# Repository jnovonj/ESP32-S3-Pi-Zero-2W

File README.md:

# ESP32-S3 Pi Zero 2 W Development Board

A compact, custom 4-layer development board built around the **ESP32-S3-WROOM-1** module, designed specifically to match the form factor and mounting layout of the **Raspberry Pi Zero 2 W**.

---

## 🚀 Key Features

* **Core Module:** Espressif **ESP32-S3-WROOM-1** (Wi-Fi 802.11 b/g/n and Bluetooth 5 / BLE) with onboard antenna.
* **Form Factor:** Drop-in compatible with Raspberry Pi Zero 2 W mounting holes and physical dimensions.
* **Dual USB-C Connectivity:**
  * **USB OTG:** Direct connection to ESP32-S3 native USB pins.
  * **USB-to-UART:** Built around the **CH343K** serial converter for flashing, debugging, and auto-reset circuitry (via dual NPN transistor configuration).
* **Power Supply:** High-efficiency **LDL1117S33R** 3.3V linear regulator powered via 5V VBUS.
* **Peripherals:** Onboard **WS2812B-Mini** addressable RGB LED for status telemetry.
* **Expansion:** 40-pin GPIO header matching standard Raspberry Pi pinout conventions.
* **Protection:** ESD protection via multiple bidirectional TVS diodes (`LESD3Z5.0C`) on data lines.

---

## ⚙️ Board Stackup (4-Layer PCB)

Designed for optimized signal integrity and solid power/ground planes:
1. **F.Cu (Top Layer):** Components and primary signal routing.
2. **In1.Cu (Internal Plane 1):** Dedicated solid **GND** plane.
3. **In2.Cu (Internal Plane 2):** Power distribution plane (`+3.3V` / `+5V`).
4. **B.Cu (Bottom Layer):** Secondary signal traces and stitching ground paths.

---

## 📂 Repository Structure

```text
├── 3D models/                # STEP models for mechanical enclosures and visualization
├── BOM/                      # Bill of Materials for manufacturing and sourcing
├── CPL/                      # Component Placement List (Pick and Place files)
├── Library/                  # Custom schematic symbols and footprints
├── database/                 # Component database files
├── images/                   # Render previews and visual assets
│   └── ESP32-S3-Pi-Zero-2W.png  # 3D PCB render preview
├── ESP32 S3 Pi Zero 2 W.kicad_pro   # KiCad project file
├── ESP32 S3 Pi Zero 2 W.kicad_sch   # Schematic design file
└── ESP32 S3 Pi Zero 2 W.kicad_pcb   # 4-layer PCB layout file

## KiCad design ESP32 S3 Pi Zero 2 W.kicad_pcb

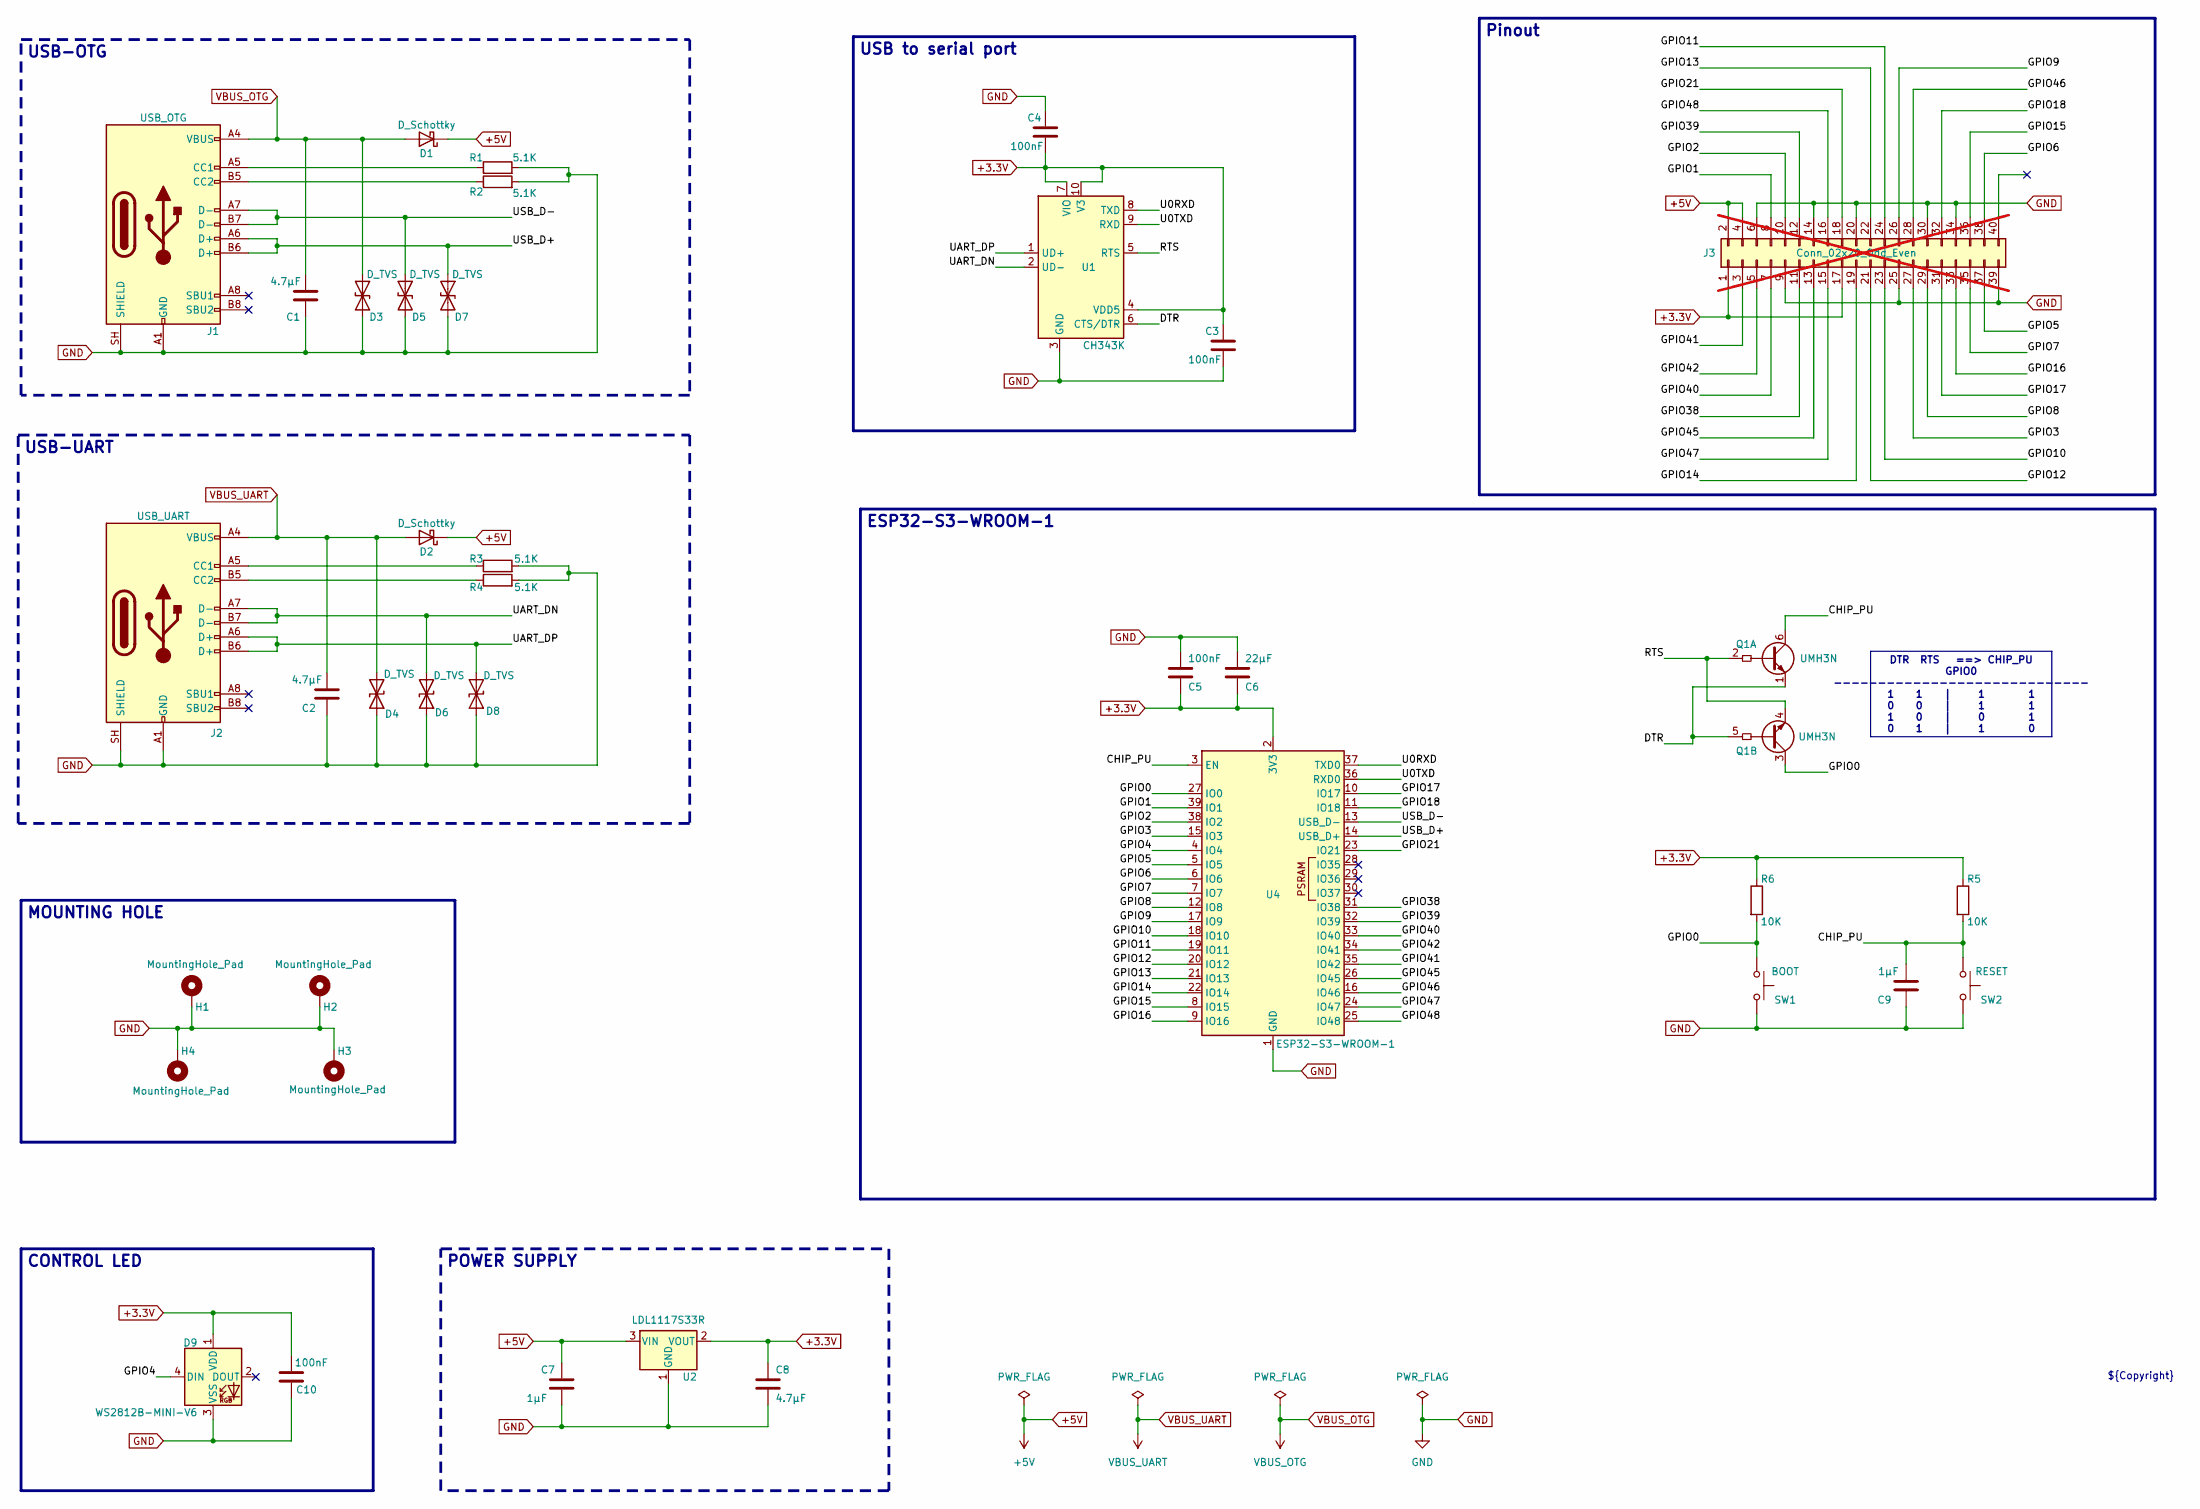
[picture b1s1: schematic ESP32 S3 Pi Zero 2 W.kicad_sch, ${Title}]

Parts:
C1, C2: 4.7µF; C_0603_1608Metric_Pad1.08x0.95mm_HandSolder; MFR.Part # HQ CA0149362
C3, C4, C10: 100nF; C_0603_1608Metric_Pad1.08x0.95mm_HandSolder; MFR.Part # HQ CA0001420
C5: 100nF; C_0603_1608Metric_Pad1.08x0.95mm_HandSolder; Mfr. Part # GRM188R71H104JA93D
C6: 22μF; C_0603_1608Metric_Pad1.08x0.95mm_HandSolder; Mfr. Part # CL10A226MP8NUNE
C7: 1μF; C_0603_1608Metric_Pad1.08x0.95mm_HandSolder; MFR.Part # HQ CA0137201
C8: 4.7µF; C_0603_1608Metric_Pad1.08x0.95mm_HandSolder; MFR.Part # HQ CA0001420
C9: 1µF; C_0603_1608Metric_Pad1.08x0.95mm_HandSolder; MFR.Part # HQ CA0137201
D1, D2: D_Schottky; D_SOD-323_HandSoldering; MFR.Part # HQ DS0183206
D3, D4, D5, D6, D7, D8: D_TVS; D_SOD-323_HandSoldering; MFR.Part # HQ UN0003855
D9: WS2812B-MINI-V6; LED_WS2812B-Mini_PLCC4_3.5x3.5mm; MFR.Part # HQ PH44591203
H1, H2, H3, H4: MountingHole_Pad; MountingHole_2.7mm_M2.5_Pad_Via
J1: USB_OTG; USB_C_Receptacle_GCT_USB4105-xx-A_16P_TopMnt_Horizontal; MFR.Part # HQ ZHLM0001696
J2: USB_UART; USB_C_Receptacle_GCT_USB4105-xx-A_16P_TopMnt_Horizontal; MFR.Part # HQ ZHLM0001696
J3: Conn_02x20_Odd_Even; PinHeader_2x20_P2.54mm_Vertical; Mfr. Part # 1; not fitted
Q1: UMH3N; SOT-363_SC-70-6; MFR.Part # HQ DS0127880
R1, R2, R3, R4: 5.1K; R_0603_1608Metric_Pad0.98x0.95mm_HandSolder; MFR.Part # HQ RE0010352
R5, R6: 10K; R_0603_1608Metric_Pad0.98x0.95mm_HandSolder; MFR.Part # HQ RE0023891
SW1: BOOT; SW_SPST_B3U-1000P; MFR.Part # HQ SW0036094
SW2: RESET; SW_SPST_B3U-1000P; MFR.Part # HQ SW0036094
U1: CH343K; SSOP-10-1EP_3.9x4.9mm_P1mm_EP2.1x3.3mm; Mfr. Part # CH343K
U2: LDL1117S33R; SOT-223-3_TabPin2; MFR.Part # HQ IC0414375
U4: ESP32-S3-WROOM-1; MFR.Part # HQ ZHLM0347370

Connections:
+3.3V: C3.1, C4.2, C5.1, C6.1, C8.1, C10.2, D9.1 (VDD), J3.1, J3.17, R5.1, R6.1, U1.4 (VDD5), U1.7 (VIO), U1.10 (V3), U2.2 (VOUT), U4.2 (3V3)
+5V: C7.1, D1.1 (K), D2.1 (K), J3.2, J3.4, U2.3 (VIN)
/CHIP_PU: C9.1, Q1.6 (C1), R5.2, SW2.1, U4.3 (EN)
/DTR: Q1.1 (E1), Q1.5 (B2), U1.6 (CTS/DTR)
/GPIO0: Q1.3 (C2), R6.2, SW1.1, U4.27 (IO0)
/GPIO1: J3.8, U4.39 (IO1)
/GPIO2: J3.10, U4.38 (IO2)
/GPIO3: J3.27, U4.15 (IO3)
/GPIO4: D9.4 (DIN), U4.4 (IO4)
/GPIO5: J3.37, U4.5 (IO5)
/GPIO6: J3.38, U4.6 (IO6)
/GPIO7: J3.35, U4.7 (IO7)
/GPIO8: J3.29, U4.12 (IO8)
/GPIO9: J3.26, U4.17 (IO9)
/GPIO10: J3.23, U4.18 (IO10)
/GPIO11: J3.24, U4.19 (IO11)
/GPIO12: J3.21, U4.20 (IO12)
/GPIO13: J3.22, U4.21 (IO13)
/GPIO14: J3.19, U4.22 (IO14)
/GPIO15: J3.36, U4.8 (IO15)
/GPIO16: J3.33, U4.9 (IO16)
/GPIO17: J3.31, U4.10 (IO17)
/GPIO18: J3.32, U4.11 (IO18)
/GPIO21: J3.18, U4.23 (IO21)
/GPIO38: J3.11, U4.31 (IO38)
/GPIO39: J3.12, U4.32 (IO39)
/GPIO40: J3.7, U4.33 (IO40)
/GPIO41: J3.3, U4.35 (IO42)
/GPIO42: J3.5, U4.34 (IO41)
/GPIO45: J3.13, U4.26 (IO45)
/GPIO46: J3.28, U4.16 (IO46)
/GPIO47: J3.15, U4.24 (IO47)
/GPIO48: J3.16, U4.25 (IO48)
/RTS: Q1.2 (B1), Q1.4 (E2), U1.5 (RTS)
/U0RXD: U1.8 (TXD), U4.37 (TXD0)
/U0TXD: U1.9 (RXD), U4.36 (RXD0)
/UART_DN: D6.2 (A2), J2.A7 (D-), J2.B7 (D-), U1.2 (UD-)
/UART_DP: D8.2 (A2), J2.A6 (D+), J2.B6 (D+), U1.1 (UD+)
/USB_D+: D7.1 (A1), J1.A6 (D+), J1.B6 (D+), U4.14 (USB_D+)
/USB_D-: D5.1 (A1), J1.A7 (D-), J1.B7 (D-), U4.13 (USB_D-)
GND: C1.1, C2.1, C3.2, C4.1, C5.2, C6.2, C7.2, C8.2, C9.2, C10.1, D3.2 (A2), D4.1 (A1), D5.2 (A2), D6.1 (A1), D7.2 (A2), D8.1 (A1), D9.3 (VSS), H1.1 (1_1), H2.1 (1_1), H3.1 (1_1), H4.1 (1_1), J1.A1 (GND), J1.A12 (GND), J1.B1 (GND), J1.B12 (GND), J1.SH (SHIELD), J2.A1 (GND), J2.A12 (GND), J2.B1 (GND), J2.B12 (GND), J2.SH (SHIELD), J3.6, J3.9, J3.14, J3.20, J3.25, J3.30, J3.34, J3.39, R1.2, R2.2, R3.2, R4.2, SW1.2, SW2.2, U1.3 (GND), U1.11 (GND), U2.1 (GND), U4.1 (GND), U4.40 (GND), U4.41 (GND)
unnamed: J1.A5 (CC1), R1.1
unnamed: J1.B5 (CC2), R2.1
unnamed: J2.A5 (CC1), R3.1
unnamed: J2.B5 (CC2), R4.1
VBUS_OTG: C1.2, D1.2 (A), D3.1 (A1), J1.A4 (VBUS), J1.A9 (VBUS), J1.B4 (VBUS), J1.B9 (VBUS)
VBUS_UART: C2.2, D2.2 (A), D4.2 (A2), J2.A4 (VBUS), J2.A9 (VBUS), J2.B4 (VBUS), J2.B9 (VBUS)

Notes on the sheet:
${Copyright}
POWER SUPPLY
ESP32-S3-WROOM-1
Pinout
MOUNTING HOLE
DTR RTS ==> CHIP_PU GPIO0 ----------------------------- 1 1 | 1 1 0 0 | 1 1 1 0 | 0 1 0 1 | 1 0
USB-OTG
USB to serial port
USB-UART
CONTROL LED

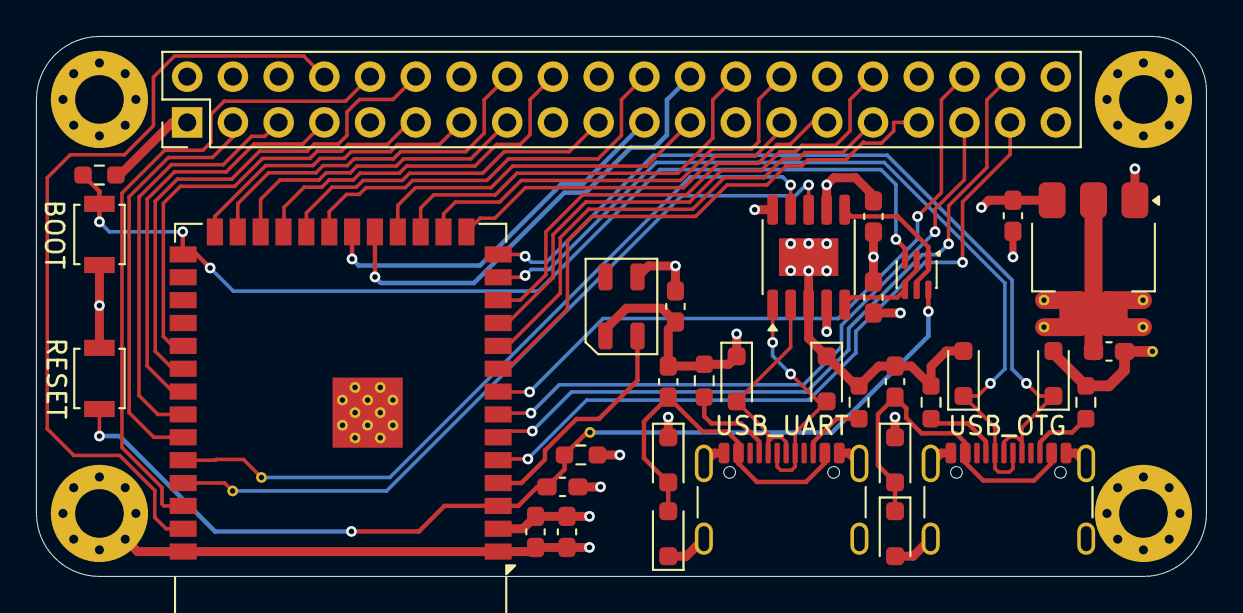
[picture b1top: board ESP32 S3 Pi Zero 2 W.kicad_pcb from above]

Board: 4 copper layers, 65.0 x 30.0 mm, 38 parts (0 on the bottom side), 47 nets.

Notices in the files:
ESP32 S3 Pi Zero 2 W.kicad_pcb:
©jnovonj, 2025
parts and their libraries:
Copyright: ©jnovonj, 2026
